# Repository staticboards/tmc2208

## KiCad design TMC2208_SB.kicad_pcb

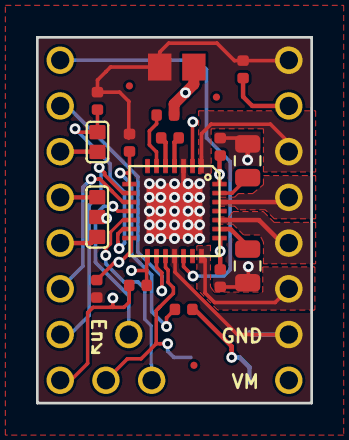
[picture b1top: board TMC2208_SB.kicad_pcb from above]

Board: 4 copper layers, 15.2 x 20.3 mm, 25 parts (1 on the bottom side), 27 nets.

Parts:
C1, C3, C4: 100n/50v; C_0402_1005Metric
C2: 4u7/6v3; C_0402_1005Metric
C5: 1U/50v; C0805
C23: 100n/50V; C_0402_1005Metric
C24: 22n/50V; C_0402_1005Metric
J1: Conn_01x08; PinHeader_1x08_P2.54mm_Vertical
J2: Conn_01x08; PinHeader_1x08_P2.54mm_Vertical_SB_size_1.524_hole_1.016
J3, J4, J5: Conn_01x01; PinHeader_1x01_P2.54mm_Vertical
JP1: SolderJumper_3_Open; JUMPER3-0402_NC
JP2: SolderJumper_2_Open; JUMPER2-0402
P22, P22#2, P23: MOUNT 3.6mm; PASSER_04MM
R1, R2, R3, R15: 10K; R_0402_1005Metric
R13, R14: R0805/0R11; R_0805_2012Metric
RV2: 20K; TRIMMER-3MM-SMD
U3: TMC2208; QFN28-PAD

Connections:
0A2: J2.3, U3.21
+5V: C2.1, R15.2, U3.8
CLK: JP2.2, R2.1, U3.13
DIAG: J3.1, U3.11
DIR: J1.1, U3.19
EN: J1.8, R3.1, U3.2
GND: C1.2, C2.2, C3.2, C4.2, C5.2, J2.2, J2.8, R1.2, R2.2, R13.1, R14.1, RV2.1, U3.3, U3.18, U3.29
INDEX: J4.1, U3.12
MSI1: J1.7, U3.9
MSI2: J1.6, U3.10
unnamed: C23.2, U3.6
unnamed: C24.1, U3.4
unnamed: C24.2, U3.5
unnamed: J1.3, JP2.1
unnamed: J1.4, JP1.1
unnamed: J1.5, JP1.3
unnamed: R13.2, U3.23
unnamed: R14.2, U3.27
unnamed: R15.1, RV2.3
OA1: J2.4, U3.24
OB1: J2.5, U3.26
OB2: J2.6, U3.1
PDN_UART: JP1.2, R1.1, U3.14
STEP: J1.2, U3.16
VIO: C1.1, J2.7, R3.2, U3.15
VM: C3.1, C4.1, C5.1, C23.1, J2.1, U3.22, U3.28
VREF: J5.1, RV2.2, U3.17

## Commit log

2018-11-08 initial
2018-11-08 silk revision, resistor clean up
2019-02-28 lots of cosmetic changes
2019-02-28 copia para imprimir
2019-02-28 misc symbols
2019-02-28 fix lib names
2019-02-28 add license
2019-02-28 version 4.0
